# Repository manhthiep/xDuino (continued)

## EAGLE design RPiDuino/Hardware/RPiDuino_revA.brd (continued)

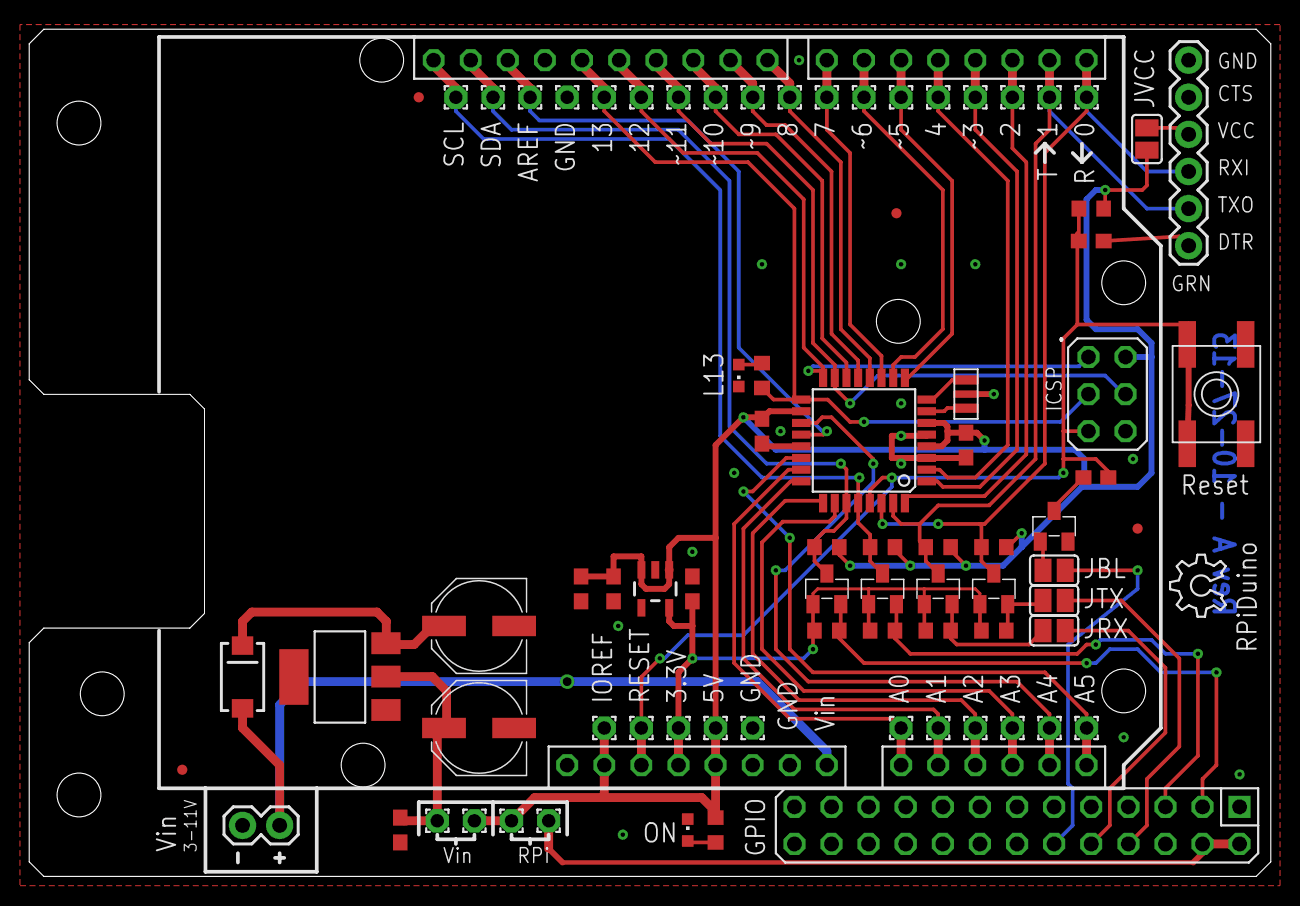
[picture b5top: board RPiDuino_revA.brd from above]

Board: 2 copper layers, 85.0 x 58.0 mm, 80 parts (0 on the bottom side), 46 nets.

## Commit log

2013-10-29 Add BBBDuino (revA), ProDuino, RPiDuino (revA)
2013-10-29 Add 324Duino, BareDuino, OLIMEX's DuinoMite, LinkDuino, RxDuino to collection
2013-10-29 Add EDuino-B of Njay (http://EmbeddedDreams.com)
2013-10-29 Add Freeduino's original designs
2013-10-29 Add Freeduino Serial/MaxSerial/SB design files
2013-10-29 Add Seeeduino
2013-10-29 Add Motoruino
2013-10-29 Add Sanguino
2013-11-27 Add ProDuino v2
2013-11-27 Add MiniDuino (original: SparkFun's ProtoSnap)
2013-11-27 Fix ProDuino v1 non-consistent
2013-11-27 Add MiniDuino's README
2013-12-14 Add MiniDuino v2
2013-12-14 Add MiniDuino's firmware
2013-12-14 Add ProDuino PTH
2013-12-14 Add ProDuino's firmware
2013-12-14 Update arduino's boards.txt for ProDuino
